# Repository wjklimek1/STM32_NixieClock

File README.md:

# STM32_NixieClock
Nixie clock based on STM32F103C8T6, DS3231 and MC34063

Nixie clock is driven by STM32F103C8T6 MCU reading data from DS3231 RTC clock. Step-up converter controlled by MC34063 produces 170V DC needed to power up display. Lamps are old japanese CD61 niexie tubes. 

Schematics and PCBs were designed with KiCad. In PDF folder you can find schematics from KiCad exported to PDF format for quick preview.

 Microcontroller program was written in C with HAL libraries and FreeRTOS. I know that any operating system is a total overkill when it comes to such a simple project but I used it to get familiar with FreeRTOS before I start more advanced projects.

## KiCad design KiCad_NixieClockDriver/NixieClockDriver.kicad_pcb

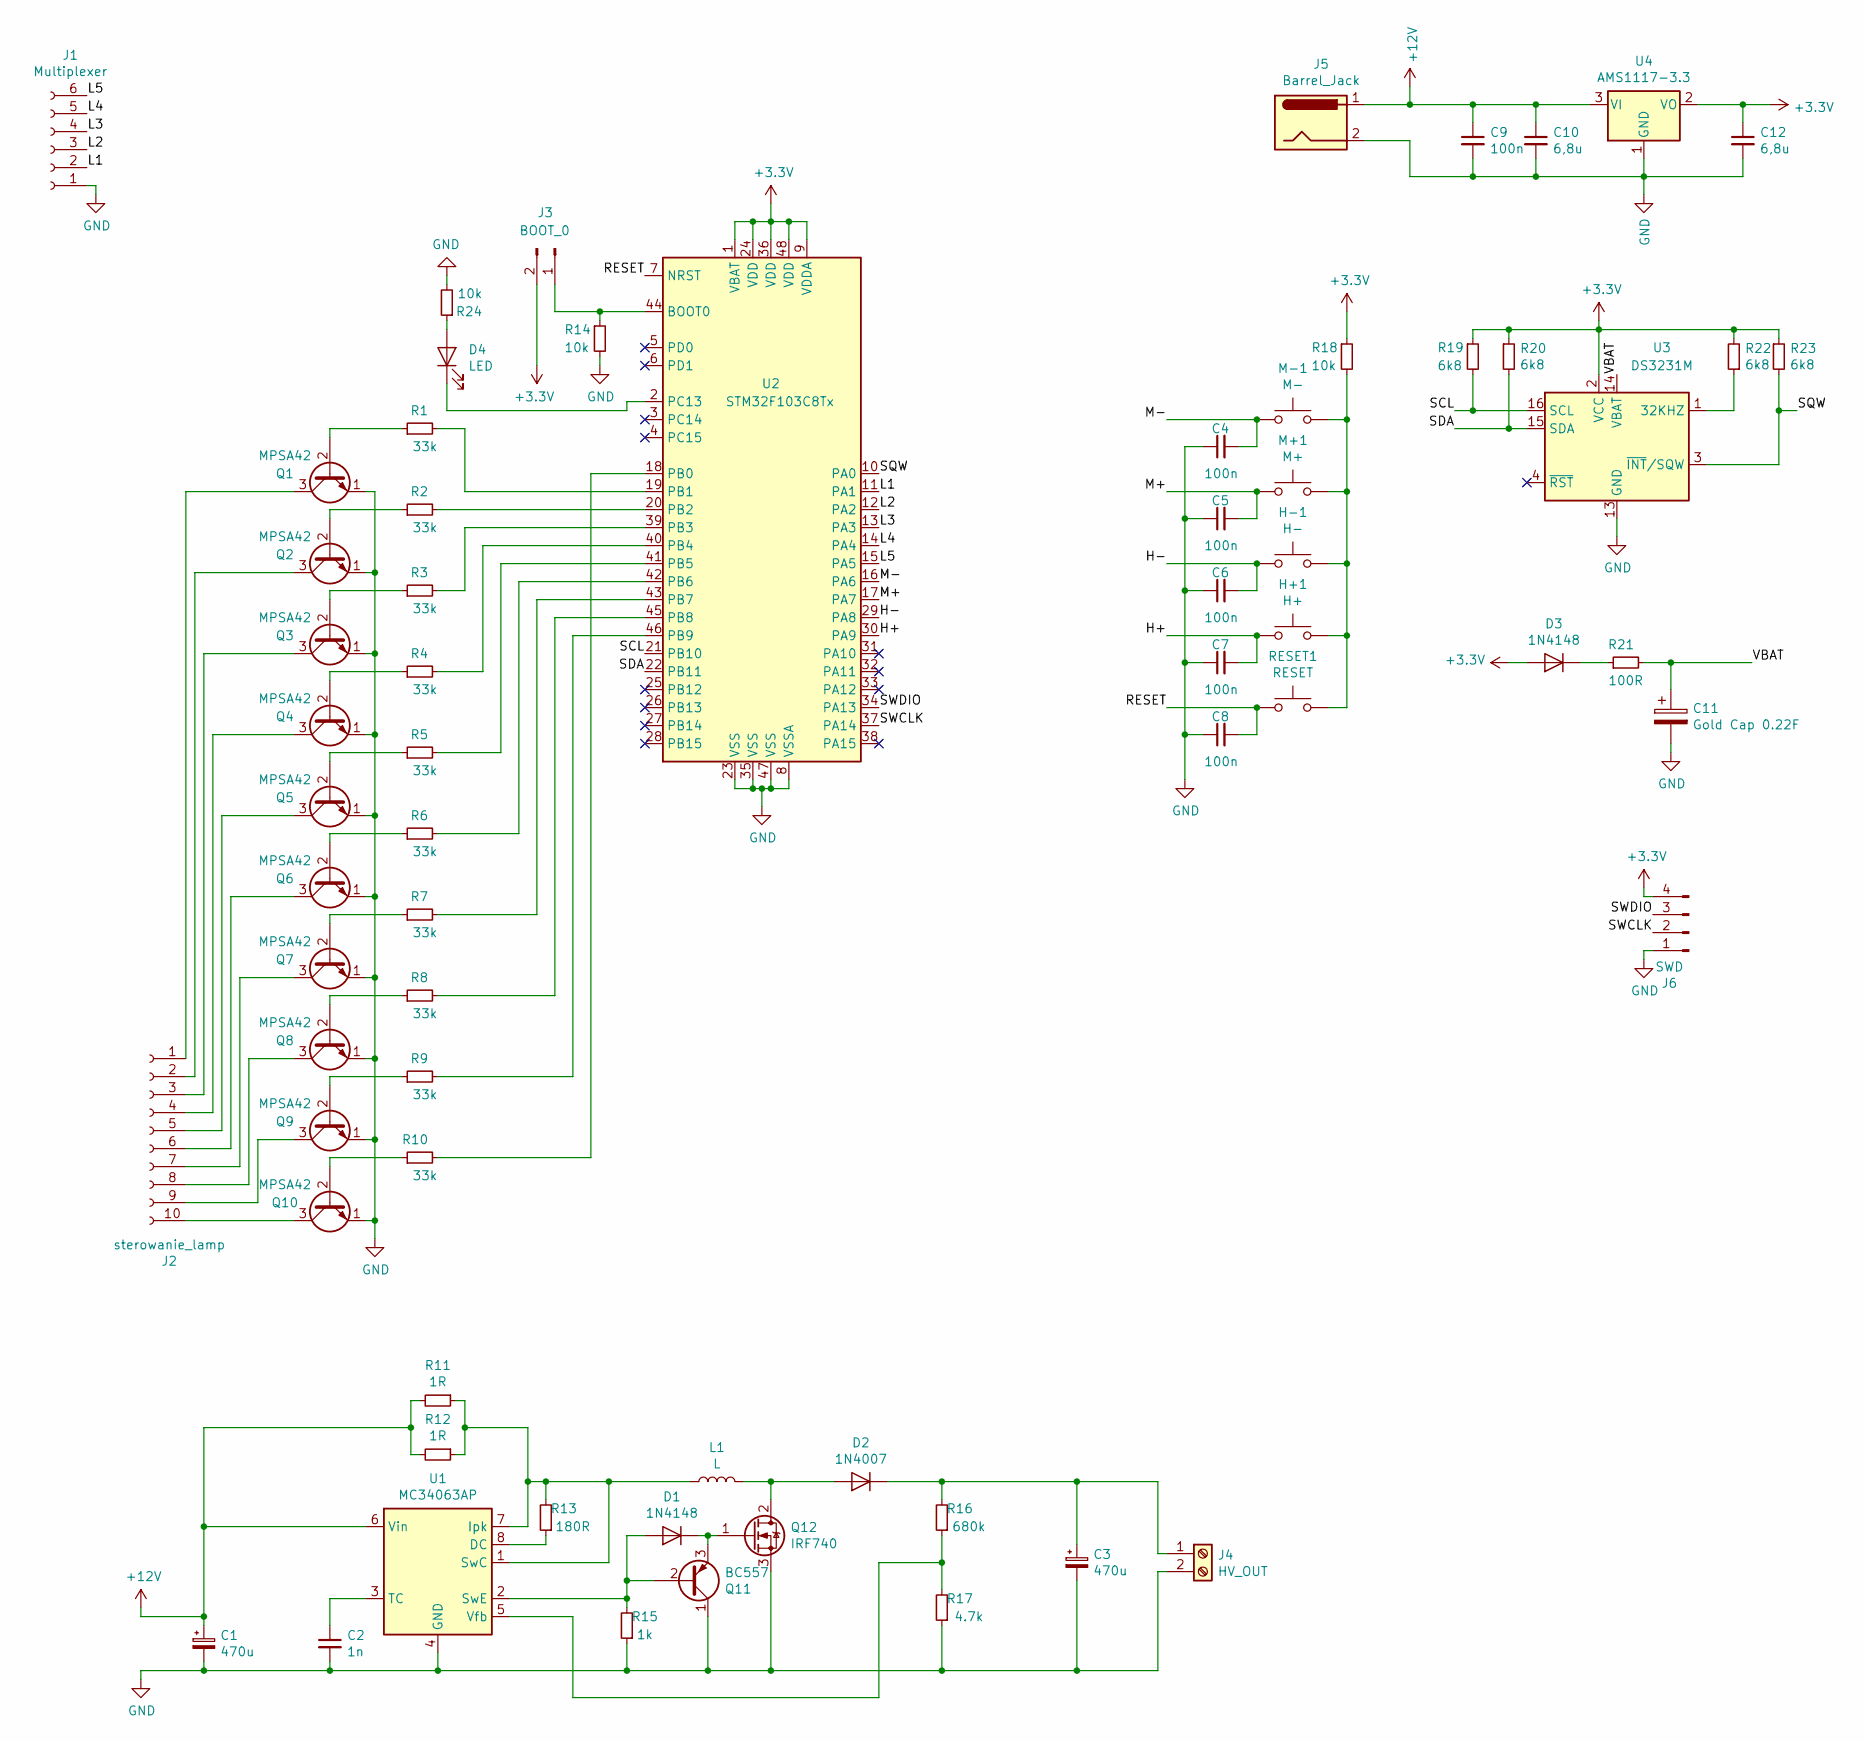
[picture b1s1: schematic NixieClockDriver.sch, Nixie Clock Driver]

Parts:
C1: 470u; CP_Radial_D10.0mm_P5.00mm
C2: 1n; C_Rect_L7.0mm_W2.0mm_P5.00mm
C3: 470u; CP_Elec_8x10.5
C4, C5, C6, C7, C8, C9: 100n; C_1206_3216Metric
C10, C12: 6,8u; C_1206_3216Metric
C11: Gold Cap 0.22F; GOLD_CAP
D1, D3: 1N4148; D_DO-35_SOD27_P7.62mm_Horizontal
D2: 1N4007; D_DO-41_SOD81_P10.16mm_Horizontal
D4: LED; LED_0805_2012Metric
H+1: H+; SW_SPST_TL3342
H-1: H-; SW_SPST_TL3342
J1: Multiplexer; PinSocket_1x06_P2.54mm_Vertical
J2: sterowanie_lamp; PinSocket_1x10_P2.54mm_Vertical
J3: BOOT_0; PinHeader_1x02_P2.54mm_Horizontal
J4: HV_OUT; TerminalBlock_bornier-2_P5.08mm
J5: Barrel_Jack; BarrelJack_Wuerth_6941xx301002
J6: SWD; PinHeader_1x04_P2.54mm_Horizontal
L1: L; L_Radial_D10.0mm_P5.00mm_Fastron_07P
M+1: M+; SW_SPST_TL3342
M-1: M-; SW_SPST_TL3342
Q1, Q2, Q3, Q4, Q5, Q6, Q7, Q8, Q9, Q10: MPSA42; TO-92_Inline
Q11: BC557; TO-92_Inline
Q12: IRF740; TO-220-3_Horizontal_TabDown
R1, R2, R3, R4, R5, R6, R7, R8, R9, R10: 33k; R_1206_3216Metric
R11, R12: 1R; R_1206_3216Metric
R13: 180R; R_1206_3216Metric
R14, R18, R24: 10k; R_1206_3216Metric
R15: 1k; R_1206_3216Metric
R16: 680k; R_1206_3216Metric
R17: 4.7k; R_1206_3216Metric
R19, R20, R22, R23: 6k8; R_1206_3216Metric
R21: 100R; R_1206_3216Metric
RESET1: RESET; SW_SPST_TL3342
U1: MC34063AP; DIP-8_W7.62mm
U2: STM32F103C8Tx; LQFP-48_7x7mm_P0.5mm
U3: DS3231M; SOIC-16W_7.5x10.3mm_P1.27mm
U4: AMS1117-3.3; SOT-223-3_TabPin2

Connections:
+3V3: C12.1, D3.2 (A), J3.2, J6.4, R18.1, R19.1, R20.1, R22.2, R23.1, U2.1 (VBAT), U2.9 (VDDA), U2.24 (VDD), U2.36 (VDD), U2.48 (VDD), U3.2 (VCC), U4.2 (VO)
+12V: C1.1, C9.1, C10.1, J5.1, R11.2, R12.2, U1.6 (Vin), U4.3 (VI)
/H+: C7.2, H+1.1, U2.30 (PA9)
/H-: C6.2, H-1.1, U2.29 (PA8)
/L1: J1.2, U2.11 (PA1)
/L2: J1.3, U2.12 (PA2)
/L3: J1.4, U2.13 (PA3)
/L4: J1.5, U2.14 (PA4)
/L5: J1.6, U2.15 (PA5)
/M+: C5.2, M+1.1, U2.17 (PA7)
/M-: C4.2, M-1.1, U2.16 (PA6)
/RESET: C8.2, RESET1.1, U2.7 (NRST)
/SCL: R19.2, U2.21 (PB10), U3.16 (SCL)
/SDA: R20.2, U2.22 (PB11), U3.15 (SDA)
/SQW: R23.2, U2.10 (PA0), U3.3 (~INT~/SQW)
/SWCLK: J6.2, U2.37 (PA14)
/SWDIO: J6.3, U2.34 (PA13)
/VBAT: C11.1, R21.2, U3.14 (VBAT)
GND: C1.2, C2.2, C3.2, C4.1, C5.1, C6.1, C7.1, C8.1, C9.2, C10.2, C11.2, C12.2, J1.1, J4.2, J5.2, J6.1, Q1.1 (E), Q2.1 (E), Q3.1 (E), Q4.1 (E), Q5.1 (E), Q6.1 (E), Q7.1 (E), Q8.1 (E), Q9.1 (E), Q10.1 (E), Q11.1 (C), Q12.3 (S), R14.2, R15.1, R17.1, R24.2, U1.4 (GND), U2.8 (VSSA), U2.23 (VSS), U2.35 (VSS), U2.47 (VSS), U3.5 (GND), U3.6 (GND), U3.7 (GND), U3.8 (GND), U3.9 (GND), U3.10 (GND), U3.11 (GND), U3.12 (GND), U3.13 (GND), U4.1 (GND)
unnamed: C2.1, U1.3 (TC)
unnamed: C3.1, D2.1 (K), J4.1, R16.2
unnamed: D1.1 (K), Q11.3 (E), Q12.1 (G)
unnamed: D1.2 (A), Q11.2 (B), R15.2, U1.2 (SwE)
unnamed: D2.2 (A), L1.2, Q12.2 (D)
unnamed: D3.1 (K), R21.1
unnamed: D4.1 (K), U2.2 (PC13)
unnamed: D4.2 (A), R24.1
unnamed: H+1.2, H-1.2, M+1.2, M-1.2, R18.2, RESET1.2
unnamed: J2.1, Q1.3 (C)
unnamed: J2.2, Q2.3 (C)
unnamed: J2.3, Q3.3 (C)
unnamed: J2.4, Q4.3 (C)
unnamed: J2.5, Q5.3 (C)
unnamed: J2.6, Q6.3 (C)
unnamed: J2.7, Q7.3 (C)
unnamed: J2.8, Q8.3 (C)
unnamed: J2.9, Q9.3 (C)
unnamed: J2.10, Q10.3 (C)
unnamed: J3.1, R14.1, U2.44 (BOOT0)
unnamed: L1.1, R11.1, R12.1, R13.2, U1.1 (SwC), U1.7 (Ipk)
unnamed: Q1.2 (B), R1.1
unnamed: Q2.2 (B), R2.1
unnamed: Q3.2 (B), R3.1
unnamed: Q4.2 (B), R4.1
unnamed: Q5.2 (B), R5.1
unnamed: Q6.2 (B), R6.1
unnamed: Q7.2 (B), R7.1
unnamed: Q8.2 (B), R8.1
unnamed: Q9.2 (B), R9.1
unnamed: Q10.2 (B), R10.1
unnamed: R1.2, U2.19 (PB1)
unnamed: R2.2, U2.20 (PB2)
unnamed: R3.2, U2.39 (PB3)
unnamed: R4.2, U2.40 (PB4)
unnamed: R5.2, U2.41 (PB5)
unnamed: R6.2, U2.42 (PB6)
unnamed: R7.2, U2.43 (PB7)
unnamed: R8.2, U2.45 (PB8)
unnamed: R9.2, U2.46 (PB9)
unnamed: R10.2, U2.18 (PB0)
unnamed: R13.1, U1.8 (DC)
unnamed: R16.1, R17.2, U1.5 (Vfb)
unnamed: R22.1, U3.1 (32KHZ)

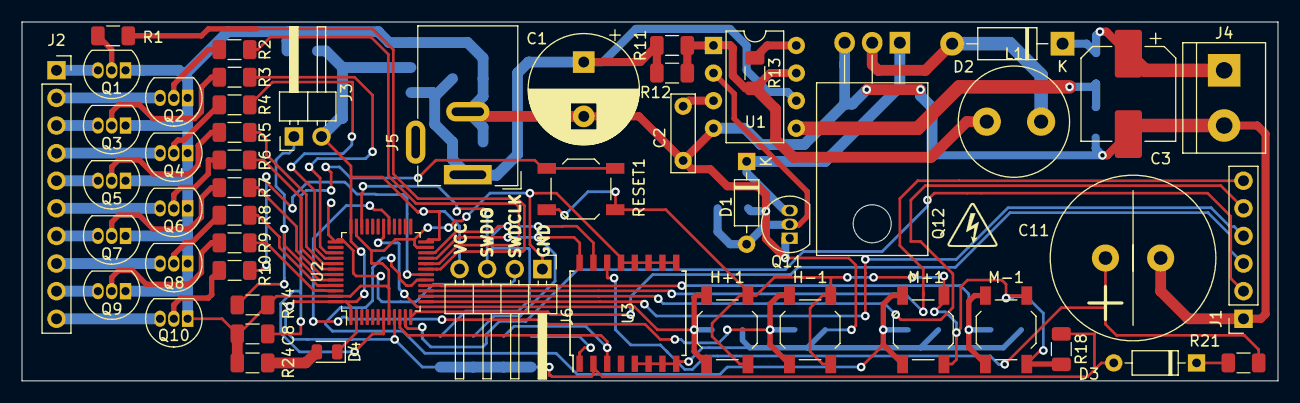
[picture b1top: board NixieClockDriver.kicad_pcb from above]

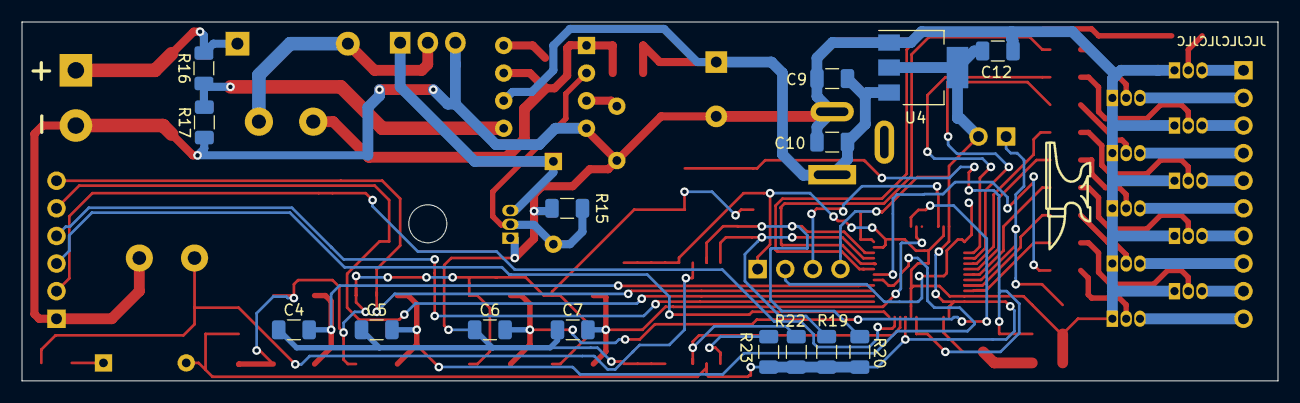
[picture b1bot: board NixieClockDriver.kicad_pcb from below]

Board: 2 copper layers, 115.6 x 33.0 mm, 68 parts (15 on the bottom side), 63 nets.

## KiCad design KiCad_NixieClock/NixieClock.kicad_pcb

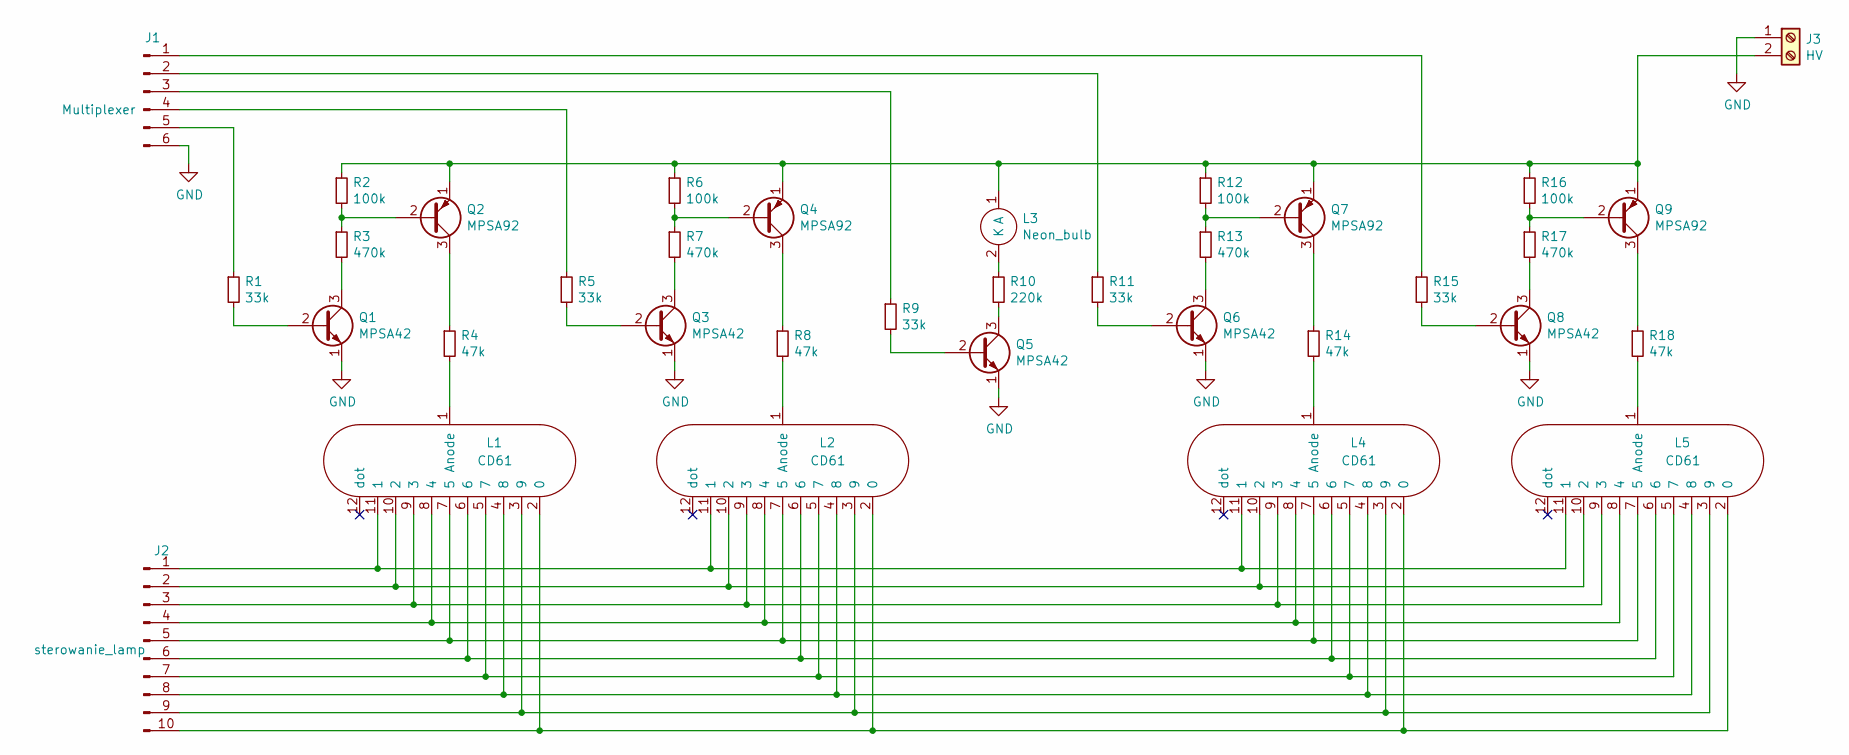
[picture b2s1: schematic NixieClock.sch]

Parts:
J1: Multiplexer; PinHeader_1x06_P2.54mm_Vertical
J2: sterowanie_lamp; PinHeader_1x10_P2.54mm_Vertical
J3: HV; TerminalBlock_bornier-2_P5.08mm
L1, L2, L4, L5: CD61; CD61_nixie
L3: Neon_bulb; neon_lamp
Q1, Q3, Q5, Q6, Q8: MPSA42; TO-92_Inline
Q2, Q4, Q7, Q9: MPSA92; TO-92_Inline
R1, R5, R9, R11, R15: 33k; R_1206_3216Metric_Pad1.42x1.75mm_HandSolder
R2, R6, R12, R16: 100k; R_1206_3216Metric_Pad1.42x1.75mm_HandSolder
R3, R7, R13, R17: 470k; R_1206_3216Metric_Pad1.42x1.75mm_HandSolder
R4, R8, R14, R18: 47k; R_1206_3216Metric_Pad1.42x1.75mm_HandSolder
R10: 220k; R_1206_3216Metric_Pad1.42x1.75mm_HandSolder

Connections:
GND: J1.6, J3.1, Q1.1 (E), Q3.1 (E), Q5.1 (E), Q6.1 (E), Q8.1 (E)
unnamed: J1.1, R15.1
unnamed: J1.2, R11.1
unnamed: J1.3, R9.1
unnamed: J1.4, R5.1
unnamed: J1.5, R1.1
unnamed: J2.1, L1.11 (1), L2.11 (1), L4.11 (1), L5.11 (1)
unnamed: J2.2, L1.10 (2), L2.10 (2), L4.10 (2), L5.10 (2)
unnamed: J2.3, L1.9 (3), L2.9 (3), L4.9 (3), L5.9 (3)
unnamed: J2.4, L1.8 (4), L2.8 (4), L4.8 (4), L5.8 (4)
unnamed: J2.5, L1.7 (5), L2.7 (5), L4.7 (5), L5.7 (5)
unnamed: J2.6, L1.6, L2.6, L4.6, L5.6
unnamed: J2.7, L1.5 (7), L2.5 (7), L4.5 (7), L5.5 (7)
unnamed: J2.8, L1.4 (8), L2.4 (8), L4.4 (8), L5.4 (8)
unnamed: J2.9, L1.3 (9), L2.3 (9), L4.3 (9), L5.3 (9)
unnamed: J2.10, L1.2 (0), L2.2 (0), L4.2 (0), L5.2 (0)
unnamed: J3.2, L3.1 (A), Q2.1 (E), Q4.1 (E), Q7.1 (E), Q9.1 (E), R2.1, R6.1, R12.1, R16.1
unnamed: L1.1 (Anode), R4.2
unnamed: L2.1 (Anode), R8.2
unnamed: L3.2 (K), R10.1
unnamed: L4.1 (Anode), R14.2
unnamed: L5.1 (Anode), R18.2
unnamed: Q1.2 (B), R1.2
unnamed: Q1.3 (C), R3.2
unnamed: Q2.2 (B), R2.2, R3.1
unnamed: Q2.3 (C), R4.1
unnamed: Q3.2 (B), R5.2
unnamed: Q3.3 (C), R7.2
unnamed: Q4.2 (B), R6.2, R7.1
unnamed: Q4.3 (C), R8.1
unnamed: Q5.2 (B), R9.2
unnamed: Q5.3 (C), R10.2
unnamed: Q6.2 (B), R11.2
unnamed: Q6.3 (C), R13.2
unnamed: Q7.2 (B), R12.2, R13.1
unnamed: Q7.3 (C), R14.1
unnamed: Q8.2 (B), R15.2
unnamed: Q8.3 (C), R17.2
unnamed: Q9.2 (B), R16.2, R17.1
unnamed: Q9.3 (C), R18.1

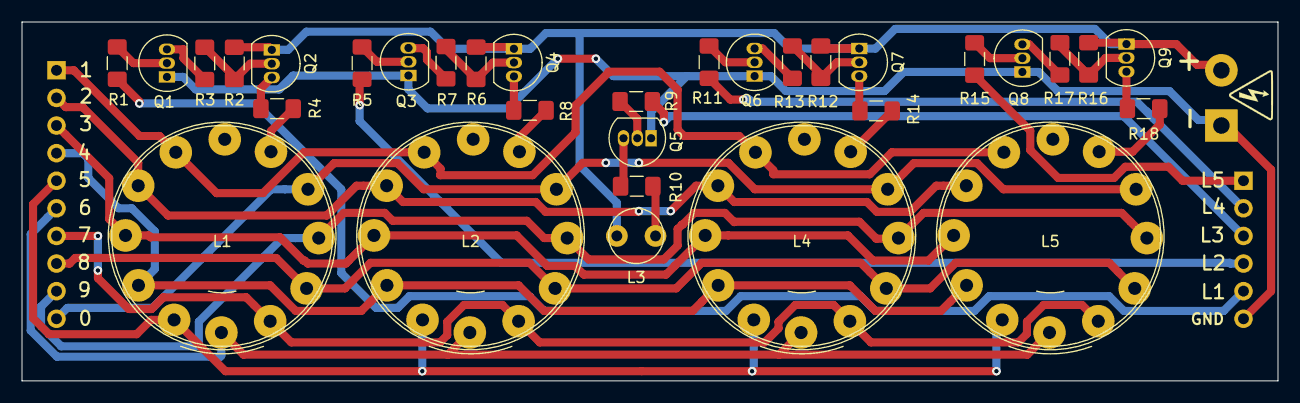
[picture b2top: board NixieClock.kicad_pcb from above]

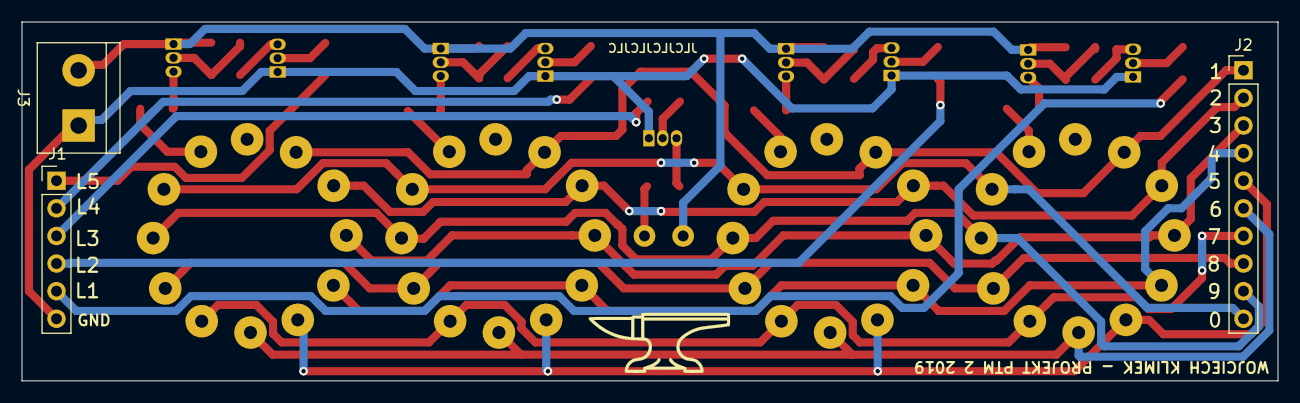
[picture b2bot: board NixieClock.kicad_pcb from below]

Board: 2 copper layers, 115.6 x 33.0 mm, 35 parts (3 on the bottom side), 40 nets.

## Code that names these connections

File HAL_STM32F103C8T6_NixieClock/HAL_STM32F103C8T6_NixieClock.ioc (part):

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Mcu.Name=STM32F103C(8-B)Tx
Mcu.Package=LQFP48
Mcu.UserName=STM32F103C8Tx
PA0-WKUP.GPIOParameters=GPIO_Label
PA0-WKUP.GPIO_Label=SQW
PA0-WKUP.Signal=GPXTI0
PA1.GPIOParameters=GPIO_Label
PA1.GPIO_Label=L1
PA1.Signal=GPIO_Output
PA13.Mode=Serial_Wire
PA13.Signal=SYS_JTMS-SWDIO
PA14.Mode=Serial_Wire
PA14.Signal=SYS_JTCK-SWCLK
PA2.GPIOParameters=GPIO_Label
PA2.GPIO_Label=L2
PA2.Signal=GPIO_Output
PA3.GPIOParameters=GPIO_Label
PA3.GPIO_Label=L3
PA3.Signal=GPIO_Output
PA4.GPIOParameters=GPIO_Label
PA4.GPIO_Label=L4
PA4.Signal=GPIO_Output
PA5.GPIOParameters=GPIO_Label
PA5.GPIO_Label=L5
PA5.Signal=GPIO_Output
PA6.GPIOParameters=GPIO_PuPd,GPIO_Label
PA6.GPIO_Label=M_MINUS
PA6.GPIO_PuPd=GPIO_PULLDOWN
PA6.Signal=GPXTI6
PA7.GPIOParameters=GPIO_PuPd,GPIO_Label
PA7.GPIO_Label=M_PLUS
PA7.GPIO_PuPd=GPIO_PULLDOWN
PA7.Signal=GPXTI7
PA8.GPIOParameters=GPIO_PuPd,GPIO_Label
PA8.GPIO_Label=H_MINUS
PA8.GPIO_PuPd=GPIO_PULLDOWN
PA8.Signal=GPXTI8
PA9.GPIOParameters=GPIO_PuPd,GPIO_Label
PA9.GPIO_Label=H_PLUS
PA9.GPIO_PuPd=GPIO_PULLDOWN
PA9.Signal=GPXTI9
PB0.GPIOParameters=GPIO_Label
PB0.GPIO_Label=N0
PB0.Signal=GPIO_Output
PB1.GPIOParameters=GPIO_Label
PB1.GPIO_Label=N1
PB1.Signal=GPIO_Output
PB10.Mode=I2C
PB10.Signal=I2C2_SCL
PB11.Mode=I2C
PB11.Signal=I2C2_SDA
PB2.GPIOParameters=GPIO_Label
PB2.GPIO_Label=N2
PB2.Signal=GPIO_Output
PB3.GPIOParameters=GPIO_Label
PB3.GPIO_Label=N3
PB3.Signal=GPIO_Output
PB4.GPIOParameters=GPIO_Label
PB4.GPIO_Label=N4
PB4.Signal=GPIO_Output
PB5.GPIOParameters=GPIO_Label
PB5.GPIO_Label=N5
PB5.Signal=GPIO_Output
PB6.GPIOParameters=GPIO_Label
PB6.GPIO_Label=N6
PB6.Signal=GPIO_Output
PB7.GPIOParameters=GPIO_Label
PB7.GPIO_Label=N7
PB7.Signal=GPIO_Output
PB8.GPIOParameters=GPIO_Label
PB8.GPIO_Label=N8
PB8.Signal=GPIO_Output
PB9.GPIOParameters=GPIO_Label
PB9.GPIO_Label=N9
PB9.Signal=GPIO_Output
PC13-TAMPER-RTC.GPIOParameters=GPIO_Label
PC13-TAMPER-RTC.GPIO_Label=LED
PC13-TAMPER-RTC.Signal=GPIO_Output
RCC.SYSCLKFreq_VALUE=64000000
RCC.SYSCLKSource=RCC_SYSCLKSOURCE_PLLCLK
board=custom

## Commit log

2020-06-23 KiCad projects for top and bottom PCB
    + KiCad project for top and bottom PCB's added
2020-06-23 Update README.md
    + Added image to readme
2020-07-08 CubeIDE project with FreeRTOS
    + peripherials initialization in CubeIDE
    + buttons handling with interrups and semaphores
    + shared memory and I2C mutexes added
2020-07-09 Readings from RTC
    + Added simple library for DS3231 RTC
    + Changing RTC time with buttons
    + Middle neon lamp now blinks with 1Hz frequency
2020-07-10 Final software version
    + Improved buttons handling
    + Added nixie tubes multiplexer
2020-07-17 Fixed reversed transistor in driver schematic
2020-07-30 Display temperature after startup
    + added "ForceConversion" function to DS3231 library. This function has to be called before "ReadTemperature" to force ADC conversion in RTC
    + display DS3231 temperature for a few seconds after startup. Useful to check temperature inside case.
2021-02-14 Schematics in PDF
    + added schematics in PDF format for quick preview without KiCad
    + small changes in component description placemnt for better readability
2021-09-05 Version modded to fit IN-8-2 lamps on the same hardware
